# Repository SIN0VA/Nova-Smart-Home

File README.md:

# Nova Smart Home
## Introduction 
This is a Home Automation project that I did for my final year, it uses a Raspberry Pi that acts as a central board for controling a bunch of Arduino UNO  cards (RF Nodes). For this project I made 4 types of these RF nodes.  

  1. [RF Switches](Arduino Sketches and Schematics/Arduino RF Controlled Lightswitch/) (to switch any electrical appliance, it's implemented here for lights only).  
  2. PIR Nodes (A bunch of Arduino's coupled with PIR detectors for autolights).  
  3. A Sensor Node (An Arduino with special [Sensor Shield](https://github.com/SIN0VA/Nova-Smart-Home/tree/master/Arduino%20Sketches%20and%20Schematics/Arduino%20Sensor%20Node) : to collect readings on temperature, humidty and somke detection ).  
  4. An HVAC Controller (An Arduino with a special [HVAC Shield](Arduino Sketches and Schematics/Arduino Sensor Node/) to   control a "Conventional HVAC System"). I haven't tested this one, so you should tread carefully.  

The communication between the Raspberry Pi and the other nodes is achieved using the NRF24L01 RF module, each type of the RF nodes has its own Shield, except the light switch which is a RF light switch (Arduino compatible) based on an Atmega328p MCU and a relay.  

## Software Stack 
### Arduino Sketches
Each RF node has its owns sketch, the two types of nodes that send data to the Raspberry Pi are the PIR Node and the Sensor Node, the other two (the HVAC controller and the RF light switch) will only recieve commands from the Raspberry Pi.  

1. [RF Switch Sketch](Arduino Sketches and Schematics/Arduino RF Controlled Lightswitch/RF LightSwitch/RF LightSwitch.ino).  
2. [PIR Node Sketch](Arduino Sketches and Schematics/Arduino RF Motion Detection/Motion Detection/Motion Detection.ino).  
3. HVAC Controller Sketch (haven't made this one).  
4. [Sensor Node Sketch](Arduino Sketches and Schematics/Arduino Sensor Node/SensorNode/SensorNode.ino).  

If you can't make the Shields, just follow the schematics of every Shield and use wires (but you have to make the RF Switch to control lights).
### Raspberry Pi  

Just to introduce the workings of this project a little bit, there are two programs ; a Node.JS app  which is an Express Web Server so people can turn off/on lights and things like that, If you're familiar with NodeJS Express check the two main files of the server the [ExpressJS Routes](HomeControlServer/routes/index.js) file and the [ExpressJS App ](HomeControlServer/app.js) file. For security reasons, this server uses SSL encryption and asks for a password and a username everytime someone tries to access this server.
The second app is a [Control Daemon](ControlDaemon/NovaHomeDaemon.cpp) coded with C++, this one controls and handles the requests from NodeJS Web Server (IPC via ZMQ sockets) and other RF nodes (via NRF24L01), it also performs the Home Automation side of things.
  
### Control Daemon Configuration  
The Nova Control Daemon is small process that controls the different RF nodes using the RF interface (NRF24L01), it waits for requests from the web server (when a user turn on/off/auto the lights from the browser). This is the heart of this system, it's the decision making engine of this Smart Home, I should note that temprature control uses a simple non-tested algorithme so this area might need some improvements. The autolights (based on motiond detection) and manual light control (using web server) work flawlessly. But this app needs a configuration, for now to configure the control daemon you have to check its [configuration file](/ControlDaemon/NovaHomeDaemon.cfg), I commented on every lines so it's pretty straightforward, later I will add the ability to configure the Dameon from a browser.

### Web Server How-To Install  
Just install NodeJS and copy the HomeControlServer. (The complete guide is coming...)

### Nova Home Daemon How-To Install  
Install the dependencies and compile NovaHomeDaemon. (Wait for the complete tutorial, it's gonna be easy)

### HomeRF Protocol 
I made this protocol to secure and manage the exchange of data and commands between the Raspberry Pi and the RF Nodes, this protocol sits on top of the RF24Network Library. It uses AES-128 for encryption and HMAC-SHA1 for authentication.
Here is a diagram for the HomeRF paquet and the structure of data encrypted inside of it :  

### Hardware Stack  
(Schematics explanations and design choices,...)

### What's working :  
These functions are tested and working properly :  
1. Autolights (motion detection, disabled/enabled at night/day).
2. Geolocation (sets the time to enable/disable the autolights function).  
3. Manual lights control from any web browser computers, tablets or smarthphones (thanks to responsive design).  
4. Secure Encryprion of RF data using the AES-128 Standard.  
5. SMS Alert in case of fire or smoke detection.  

### What's not Working :  
1. HMAC-SHA1 Authentication (gotta fix it).  
2. I haven't tested temprature and humidity control (the algorithme needs some improvment maybe a PID code).  
3. Call2Report (call the Smart Home and then it will report back with an SMS), this one is not tested.  

### IMPORTANT NOTE !
You can't sell, publish any of the code in here, it's free software under the GPLv3 licence.
Read the licence for more information.
When you use this project or any code of it especially in an academic paper, you have to link to this website.

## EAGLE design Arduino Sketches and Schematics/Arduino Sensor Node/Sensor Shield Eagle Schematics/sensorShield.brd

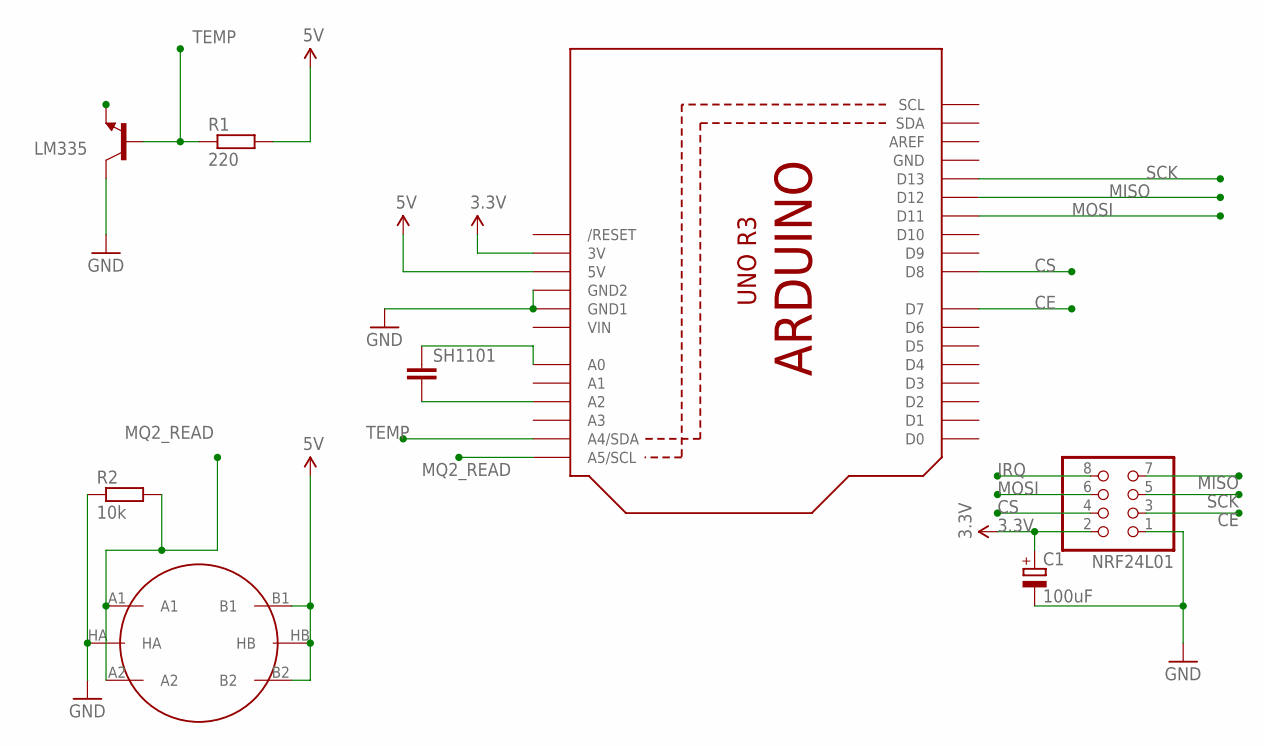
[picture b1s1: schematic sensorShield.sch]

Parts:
C1: 100uF; E5-6
LM335: TRANSISTOR_NPNTO-92-AMMO; TO-92-AMMO
NRF24L01: PINHD-2X4; 2X04
Q1: ARDUINOR3-NOIOREF-NOTEXT; ARDUINOR3-NOTEXT-NOIOREF
R1: 220; 0204/7
R2: 10k; 0204/7
SH1101: C-EU050-024X044; C050-024X044
U$1: METHANE_SENSOR; MQ-3

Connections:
3.3V: C1.+, NRF24L01.2, Q1.3V
5V: Q1.5V, R1.2, U$1.B1, U$1.B2, U$1.HB
CE: NRF24L01.3, Q1.D7
CS: NRF24L01.4, Q1.D8
GND: C1.-, LM335.3 (C), NRF24L01.1, Q1.GND, Q1.GND1, Q1.GND2, R2.1, U$1.HA
IRQ: NRF24L01.8
MISO: NRF24L01.7, Q1.D12
MOSI: NRF24L01.6, Q1.D11
MQ2_READ: Q1.A5 (A5/SCL), R2.2, U$1.A1, U$1.A2
unnamed: Q1.A2, SH1101.2
unnamed: Q1.A0, SH1101.1
SCK: NRF24L01.5, Q1.D13
TEMP: LM335.2 (B), Q1.A4 (A4/SDA), R1.1
VIN: Q1.VIN

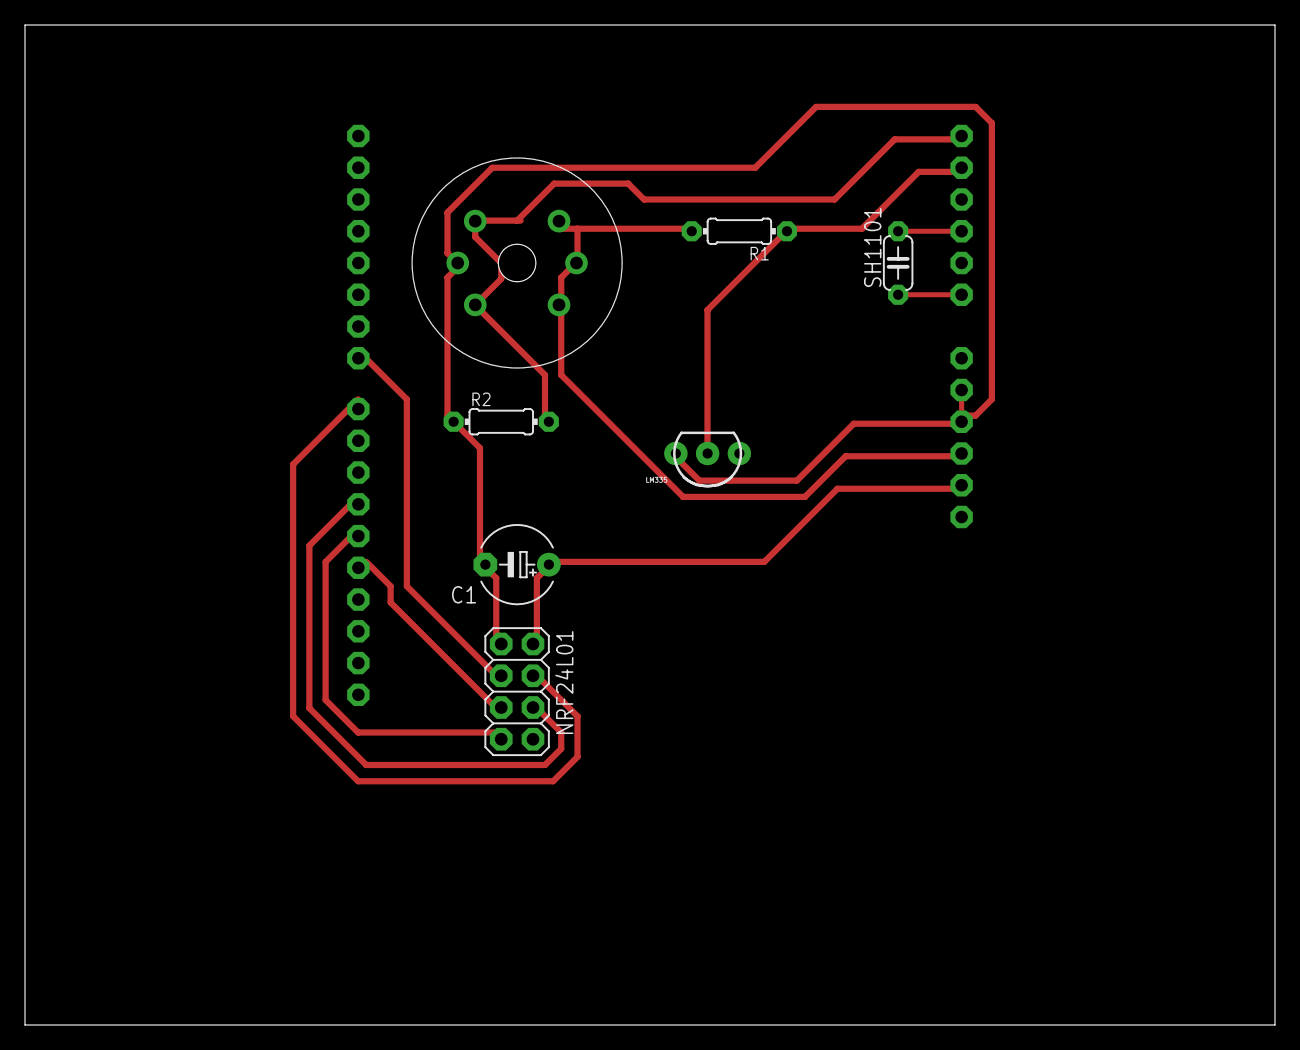
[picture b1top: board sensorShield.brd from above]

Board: 2 copper layers, 100.0 x 80.0 mm, 8 parts (0 on the bottom side), 12 nets.

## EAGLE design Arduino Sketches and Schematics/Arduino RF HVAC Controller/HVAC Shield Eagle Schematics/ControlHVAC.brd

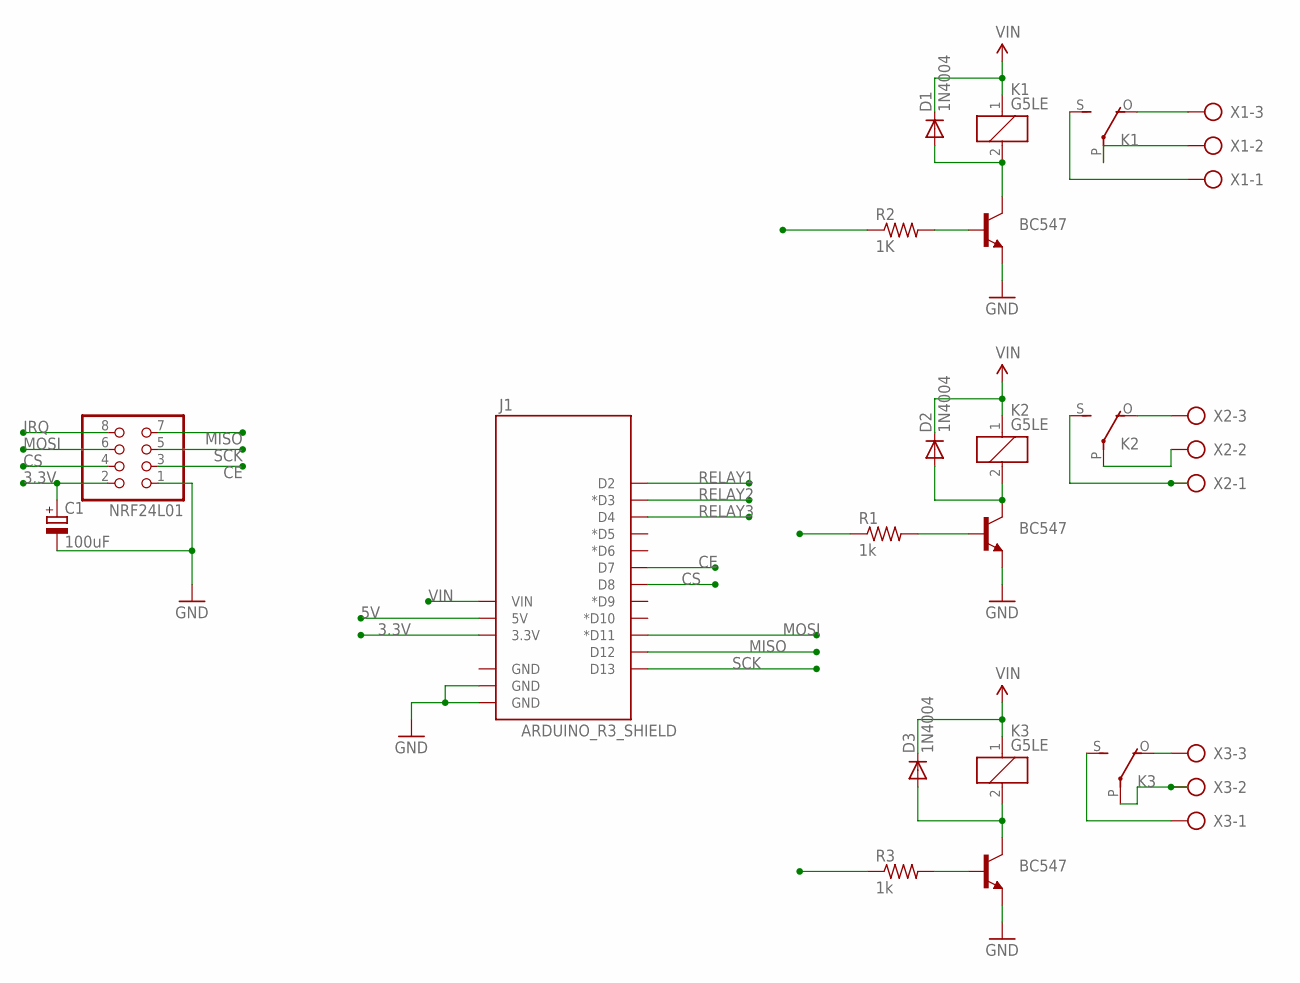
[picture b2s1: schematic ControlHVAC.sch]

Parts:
C1: 100uF; E5-6
D1, D2, D3: 1N4004; DO41-10
J1: ARDUINO_R3_SHIELD; UNO_R3_SHIELD
K1, K2, K3: G5LE
NRF24L01: PINHD-2X4; 2X04
R1, R3: 1k; 0204/7
R2: 1K; 0204/7
T1, T2, T3: BC547; TO92
X1, X2, X3: AK500/3-H

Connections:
3.3V: C1.+, J1.3.3V, NRF24L01.2
5V: J1.5V
CE: J1.D7, NRF24L01.3
CS: J1.D8, NRF24L01.4
GND: C1.-, J1.GND@0 (GND), J1.GND@1 (GND), NRF24L01.1, T1.1 (E), T2.1 (E), T3.1 (E)
IRQ: NRF24L01.8
MISO: J1.D12, NRF24L01.7
MOSI: J1.D11 (*D11), NRF24L01.6
unnamed: D3.A, K3.2, T3.3 (C)
unnamed: D2.A, K2.2, T2.3 (C)
unnamed: D1.A, K1.2, T1.3 (C)
unnamed: K2.O, X2.3
unnamed: K2.P, X2.2
unnamed: K2.S, X2.1
unnamed: K3.O, X3.3
unnamed: K3.P, X3.2
unnamed: K3.S, X3.1
unnamed: K1.S, X1.1
unnamed: K1.P, X1.2
unnamed: K1.O, X1.3
unnamed: R2.2, T1.2 (B)
unnamed: R1.2, T2.2 (B)
unnamed: R3.2, T3.2 (B)
RELAY1: J1.D2, R2.1
RELAY2: J1.D3 (*D3), R1.1
RELAY3: J1.D4, R3.1
SCK: J1.D13, NRF24L01.5
VIN: D1.C, D2.C, D3.C, J1.VIN, K1.1, K2.1, K3.1

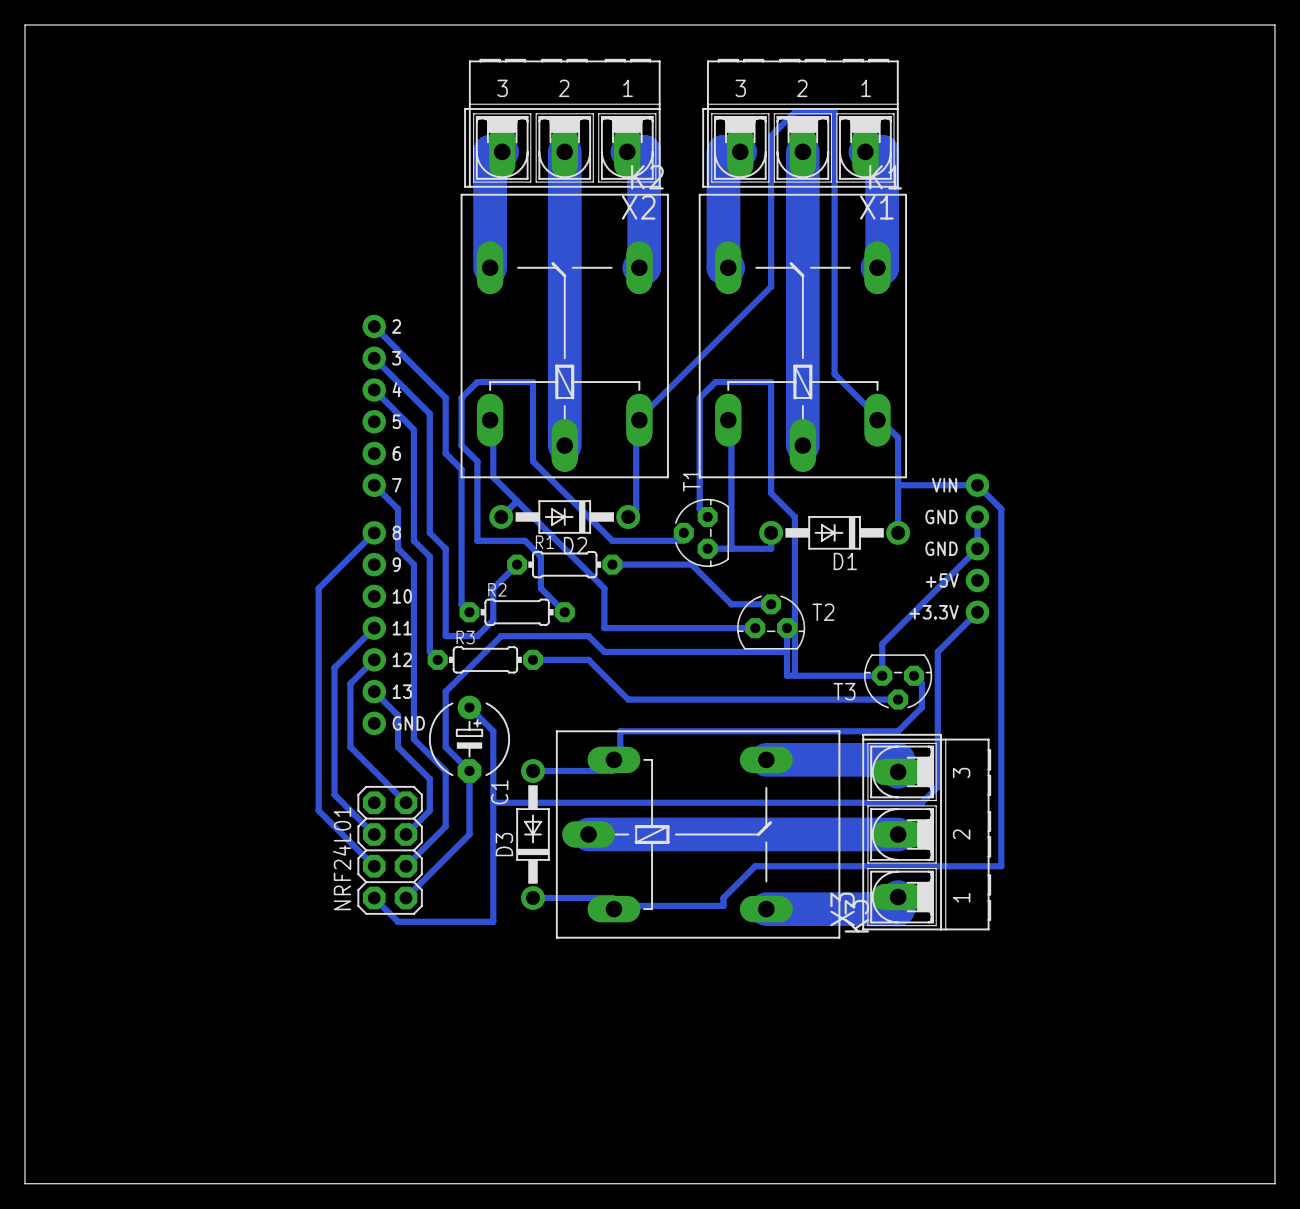
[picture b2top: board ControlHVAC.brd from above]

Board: 2 copper layers, 100.0 x 92.7 mm, 18 parts (0 on the bottom side), 26 nets.

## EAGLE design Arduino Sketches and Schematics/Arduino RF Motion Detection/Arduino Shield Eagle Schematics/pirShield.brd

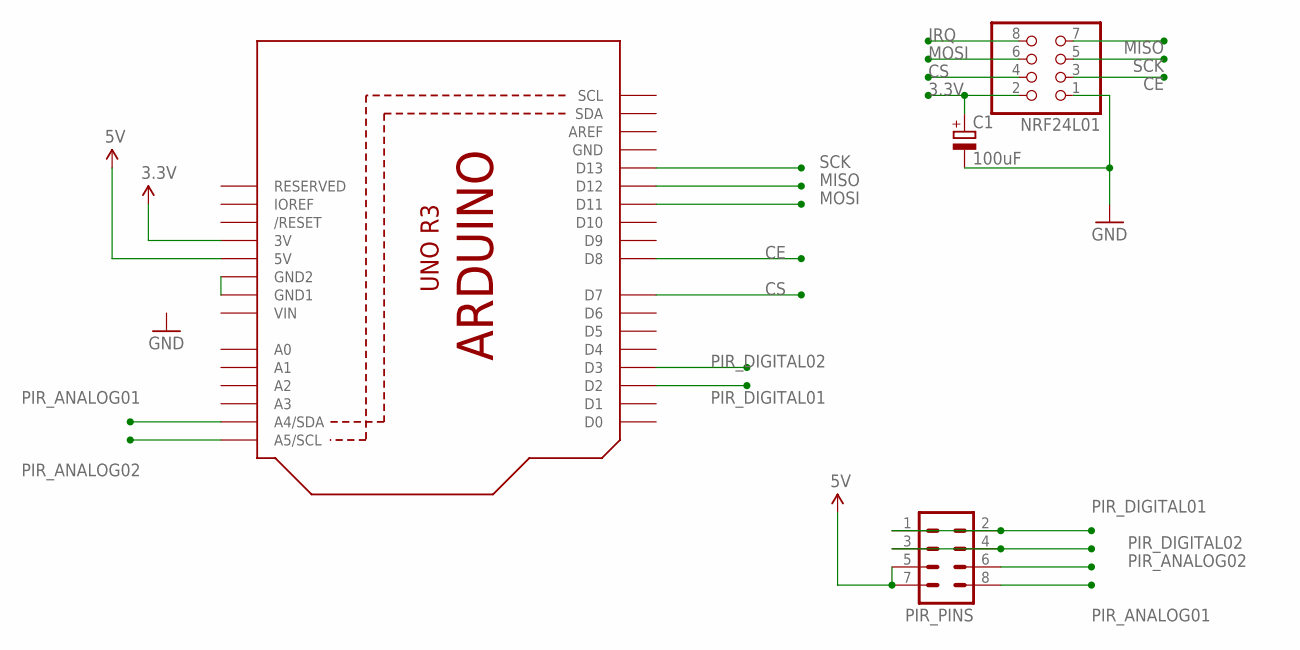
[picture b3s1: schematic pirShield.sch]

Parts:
C1: 100uF; E5-6
NRF24L01: PINHD-2X4; 2X04
PIR_PINS: MA04-2
U1: ARDUINOR3-BPLACE

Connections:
3.3V: C1.+, NRF24L01.2, U1.3V
5V: PIR_PINS.5, PIR_PINS.7, U1.5V
CE: NRF24L01.3, U1.D8
CS: NRF24L01.4, U1.D7
GND: C1.-, NRF24L01.1, U1.GND
IRQ: NRF24L01.8
MISO: NRF24L01.7, U1.D12
MOSI: NRF24L01.6, U1.D11
unnamed: U1.GND1, U1.GND2
PIR_ANALOG01: PIR_PINS.8, U1.A4 (A4/SDA)
PIR_ANALOG02: PIR_PINS.6, U1.A5 (A5/SCL)
PIR_DIGITAL01: PIR_PINS.1, PIR_PINS.2, U1.D2
PIR_DIGITAL02: PIR_PINS.3, PIR_PINS.4, U1.D3
SCK: NRF24L01.5, U1.D13
VIN: U1.VIN

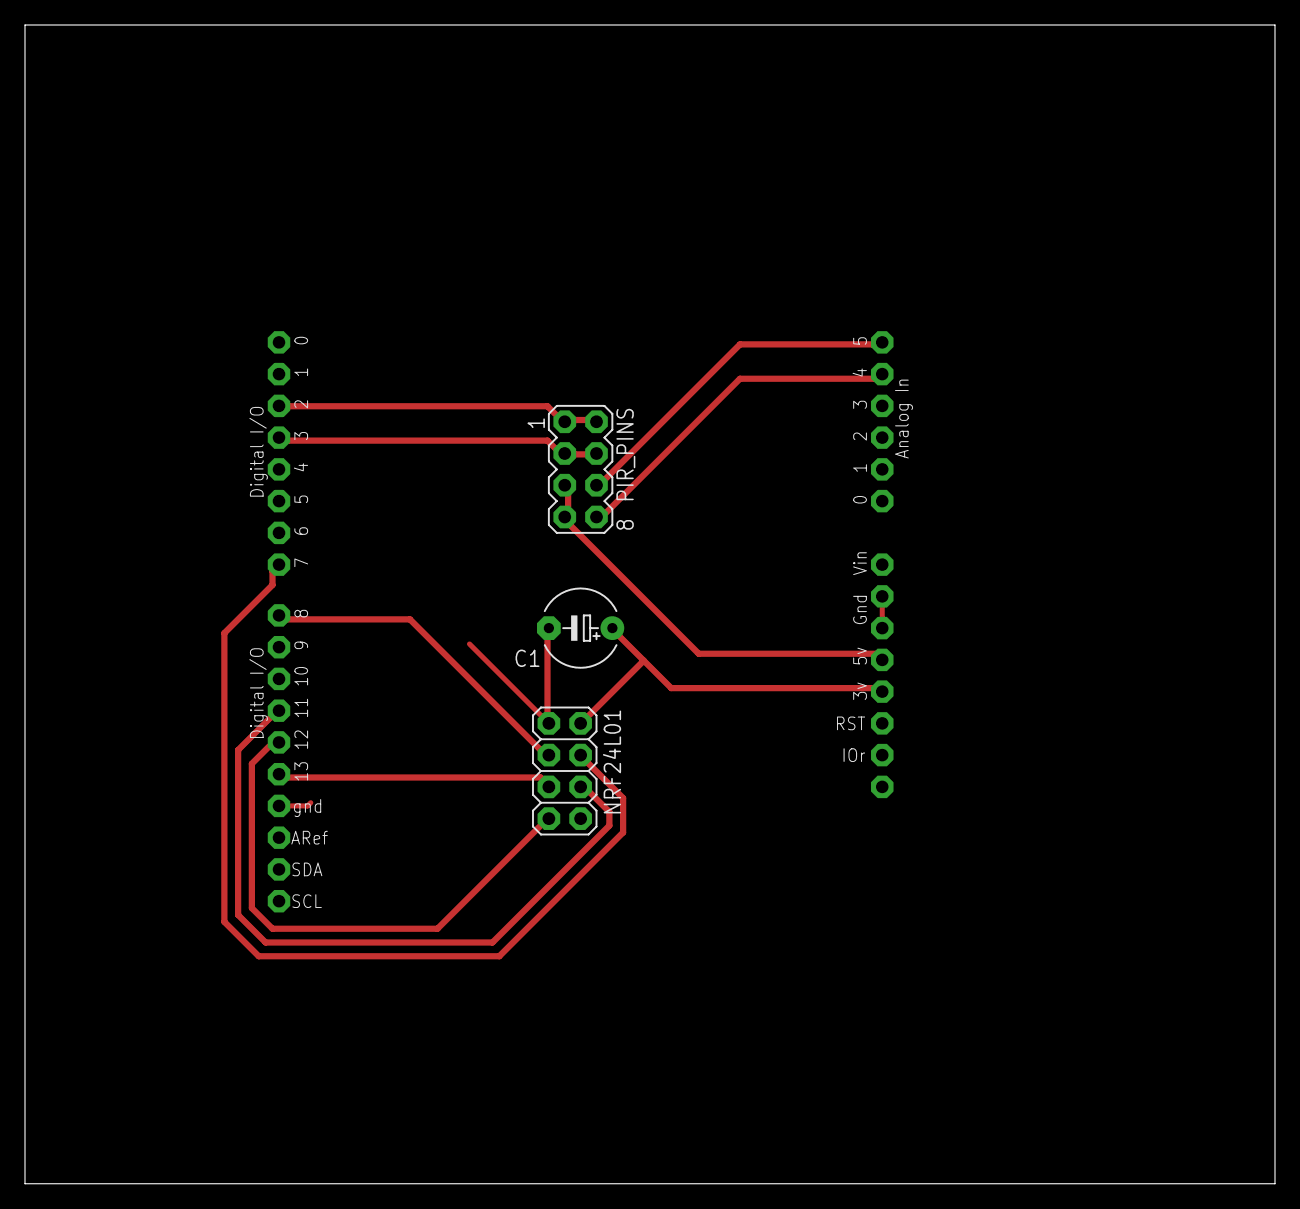
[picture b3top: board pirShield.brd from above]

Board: 2 copper layers, 100.0 x 92.7 mm, 4 parts (0 on the bottom side), 13 nets.

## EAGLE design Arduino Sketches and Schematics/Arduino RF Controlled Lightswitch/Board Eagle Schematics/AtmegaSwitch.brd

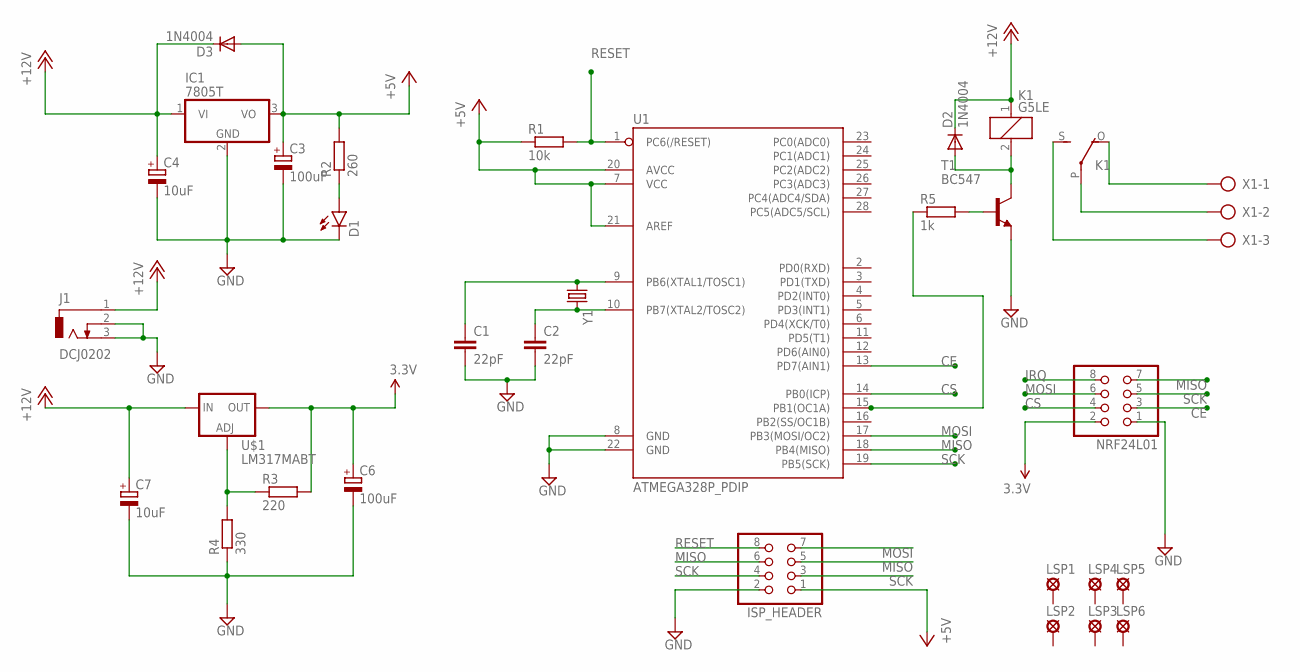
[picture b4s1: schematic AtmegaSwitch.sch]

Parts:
C1: 22pF; C025-025X050
C2: 22pF; C025-024X044
C3, C6: 100uF; E5-6
C4, C7: 10uF; E5-6
D1: LED5MM
D2, D3: 1N4004; DO41-10
IC1: 7805T; TO220H
ISP_HEADER: PINHD-2X4; 2X04
J1: DCJ0202
K1: G5LE
LSP1, LSP2, LSP3, LSP4, LSP5, LSP6: LSP10
NRF24L01: PINHD-2X4; 2X04
R1: 10k; 0204/7
R2: 260; 0204/7
R3: 220; 0204/7
R4: 330; 0204/7
R5: 1k; 0204/7
T1: BC547; TO92
U1: ATMEGA328P_PDIP; DIL28-3
U$1: LM317MABT; TO220L1
X1: AK500/3-H
Y1: CRYSTALHC49US; HC49US

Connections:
3.3V: C6.+, NRF24L01.2, R3.2, U$1.2 (OUT)
+5V: C3.+, D3.A, IC1.3 (VO), ISP_HEADER.1, R1.1, R2.2, U1.7 (VCC), U1.20 (AVCC), U1.21 (AREF)
+12V: C4.+, C7.+, D2.C, D3.C, IC1.1 (VI), J1.1, K1.1, U$1.3 (IN)
CE: NRF24L01.3, U1.13 (PD7(AIN1))
CS: NRF24L01.4, U1.14 (PB0(ICP))
GND: C1.2, C2.2, C3.-, C4.-, C6.-, C7.-, D1.K (C), IC1.2 (GND), ISP_HEADER.2, J1.2, J1.3, NRF24L01.1, R4.1, T1.1 (E), U1.8 (GND), U1.22 (GND)
IRQ: NRF24L01.8
MISO: ISP_HEADER.5, ISP_HEADER.6, NRF24L01.7, U1.18 (PB4(MISO))
MOSI: ISP_HEADER.7, NRF24L01.6, U1.17 (PB3(MOSI/OC2))
unnamed: C1.1, U1.9 (PB6(XTAL1/TOSC1)), Y1.1
unnamed: C2.1, U1.10 (PB7(XTAL2/TOSC2)), Y1.2
unnamed: D1.A, R2.1
unnamed: D2.A, K1.2, T1.3 (C)
unnamed: K1.P, X1.2
unnamed: K1.O, X1.1
unnamed: K1.S, X1.3
unnamed: R3.1, R4.2, U$1.1 (ADJ)
unnamed: R5.2, T1.2 (B)
unnamed: R5.1, U1.15 (PB1(OC1A))
RESET: ISP_HEADER.8, R1.2, U1.1 (PC6(/RESET))
SCK: ISP_HEADER.3, ISP_HEADER.4, NRF24L01.5, U1.19 (PB5(SCK))

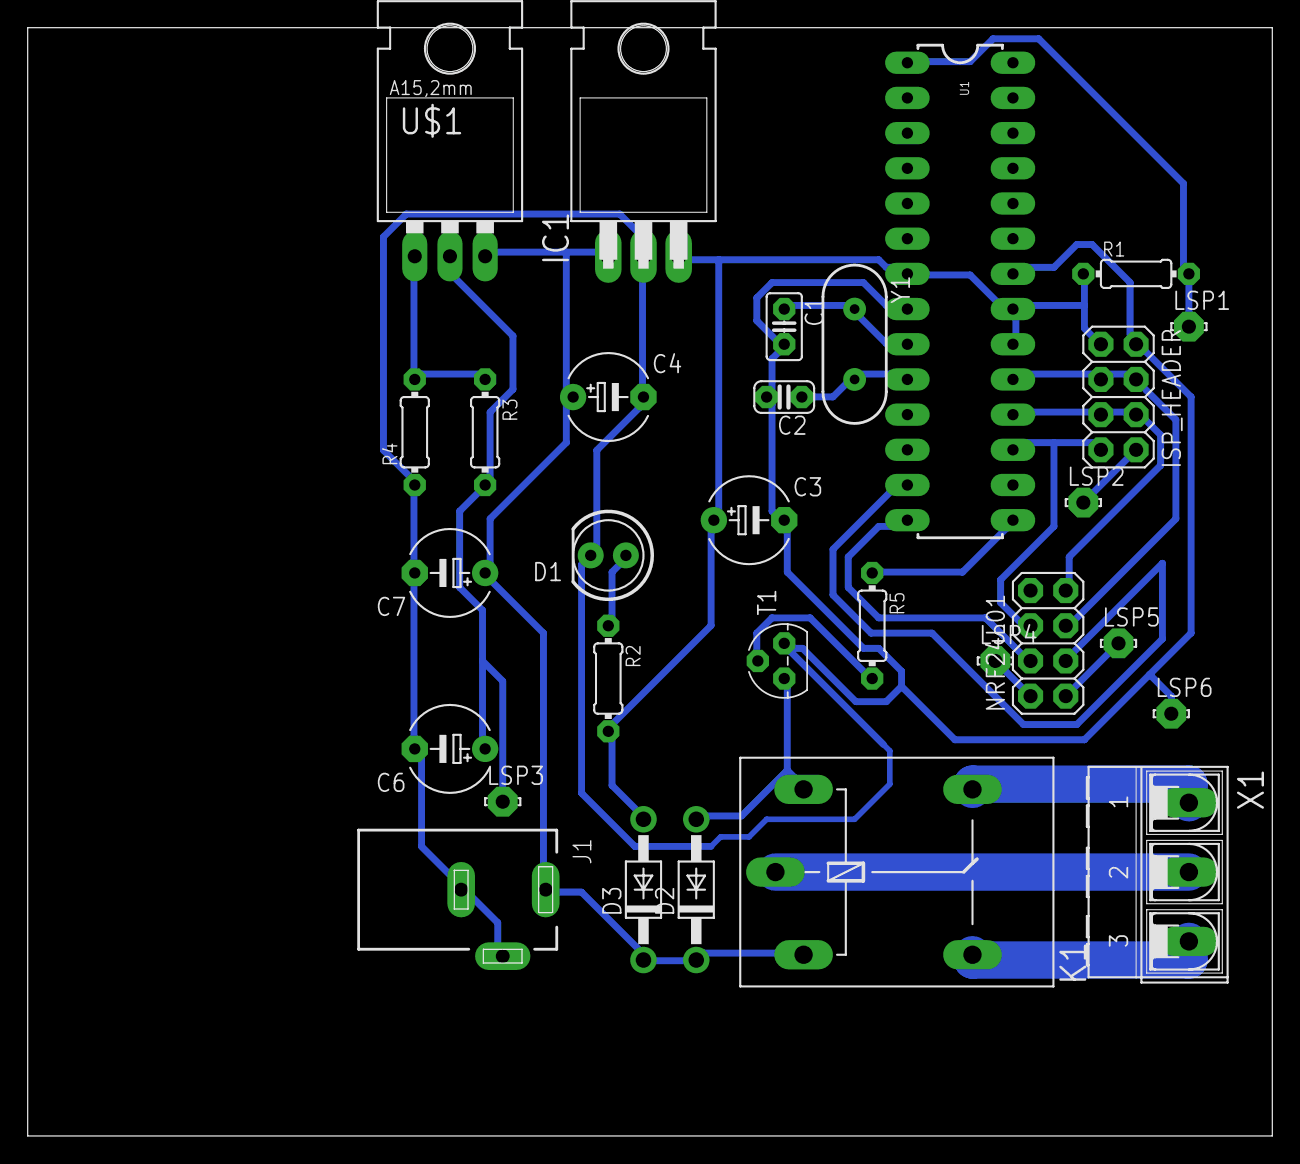
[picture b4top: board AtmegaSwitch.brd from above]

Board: 2 copper layers, 89.8 x 80.0 mm, 30 parts (0 on the bottom side), 20 nets.

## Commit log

2015-05-12 :circus_tent: Added .gitattributes
2015-05-12 First_Upload
2015-05-12 Arduino related uploads
2015-05-12 Rename hub.cfg to NovaHomeDaemon.cfg
2019-12-25 Bump morgan from 1.5.3 to 1.9.1 in /HomeControlServer
    Bumps [morgan](https://github.com/expressjs/morgan) from 1.5.3 to 1.9.1.
    - [Release notes](https://github.com/expressjs/morgan/releases)
    - [Changelog](https://github.com/expressjs/morgan/blob/master/HISTORY.md)
    - [Commits](https://github.com/expressjs/morgan/compare/1.5.3...1.9.1)
2019-12-25 Bump debug from 2.1.3 to 4.1.1 in /HomeControlServer
    Bumps [debug](https://github.com/visionmedia/debug) from 2.1.3 to 4.1.1.
    - [Release notes](https://github.com/visionmedia/debug/releases)
    - [Commits](https://github.com/visionmedia/debug/compare/2.1.3...4.1.1)

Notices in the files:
parts and their libraries:
SparkFun-LED: Licensing: Creative Commons ShareAlike 4.0 International - https://creativecommons.org/licenses/by-sa/4.0
